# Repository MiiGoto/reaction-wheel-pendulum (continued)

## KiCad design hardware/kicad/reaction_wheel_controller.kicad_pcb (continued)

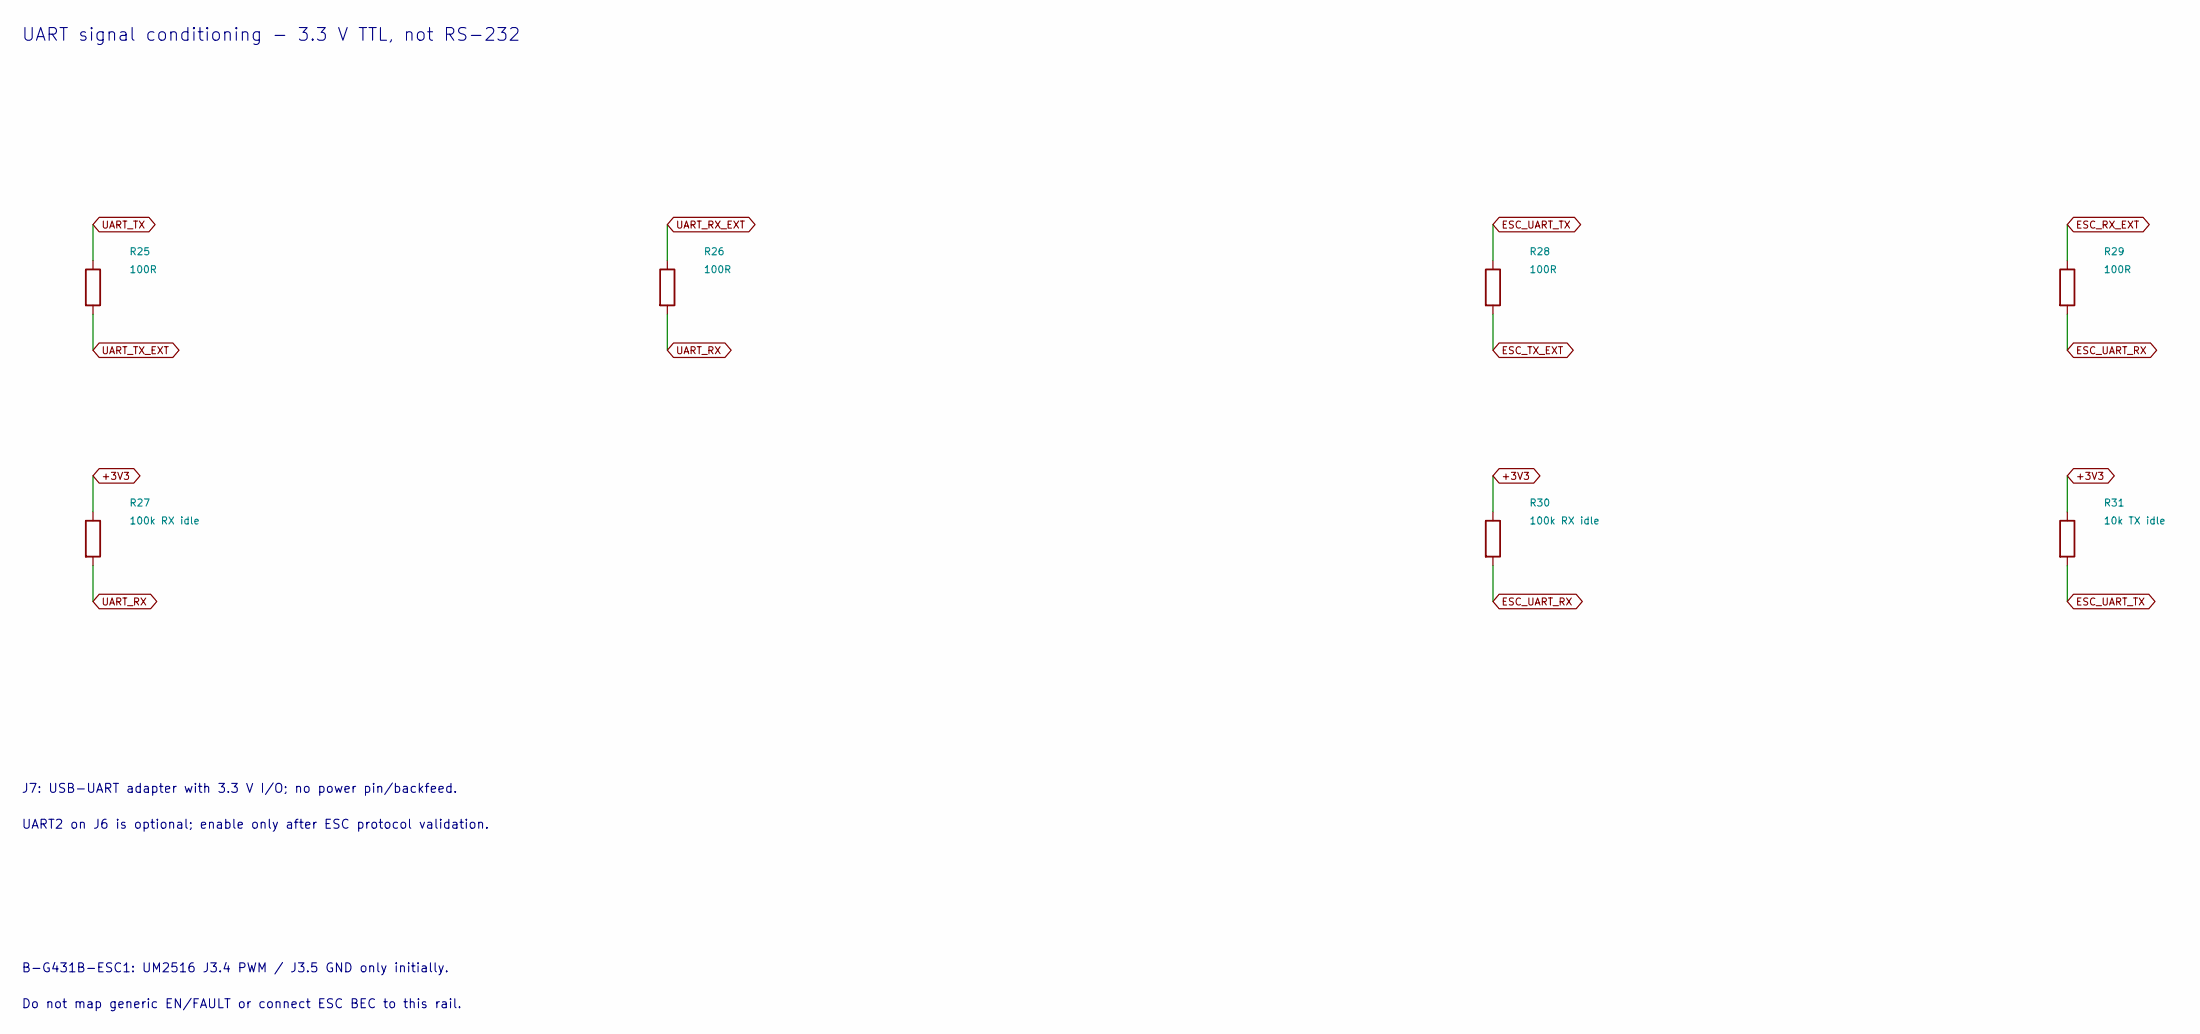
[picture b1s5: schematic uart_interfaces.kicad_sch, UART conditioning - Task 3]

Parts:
R25, R26, R28, R29: 100R; R_0805_2012Metric
R27, R30: 100k RX idle; R_0805_2012Metric
R31: 10k TX idle; R_0805_2012Metric

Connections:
+3V3: R27.1, R30.1, R31.1; also elsewhere on the board
ESC_RX_EXT: R29.1; also elsewhere on the board
ESC_TX_EXT: R28.2; also elsewhere on the board
ESC_UART_RX: R29.2, R30.2; also elsewhere on the board
ESC_UART_TX: R28.1, R31.2; also elsewhere on the board
UART_RX: R26.2, R27.2; also elsewhere on the board
UART_RX_EXT: R26.1; also elsewhere on the board
UART_TX: R25.1; also elsewhere on the board
UART_TX_EXT: R25.2; also elsewhere on the board

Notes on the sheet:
UART signal conditioning - 3.3 V TTL, not RS-232
J7: USB-UART adapter with 3.3 V I/O; no power pin/backfeed.
UART2 on J6 is optional; enable only after ESC protocol validation.
B-G431B-ESC1: UM2516 J3.4 PWM / J3.5 GND only initially.
Do not map generic EN/FAULT or connect ESC BEC to this rail.

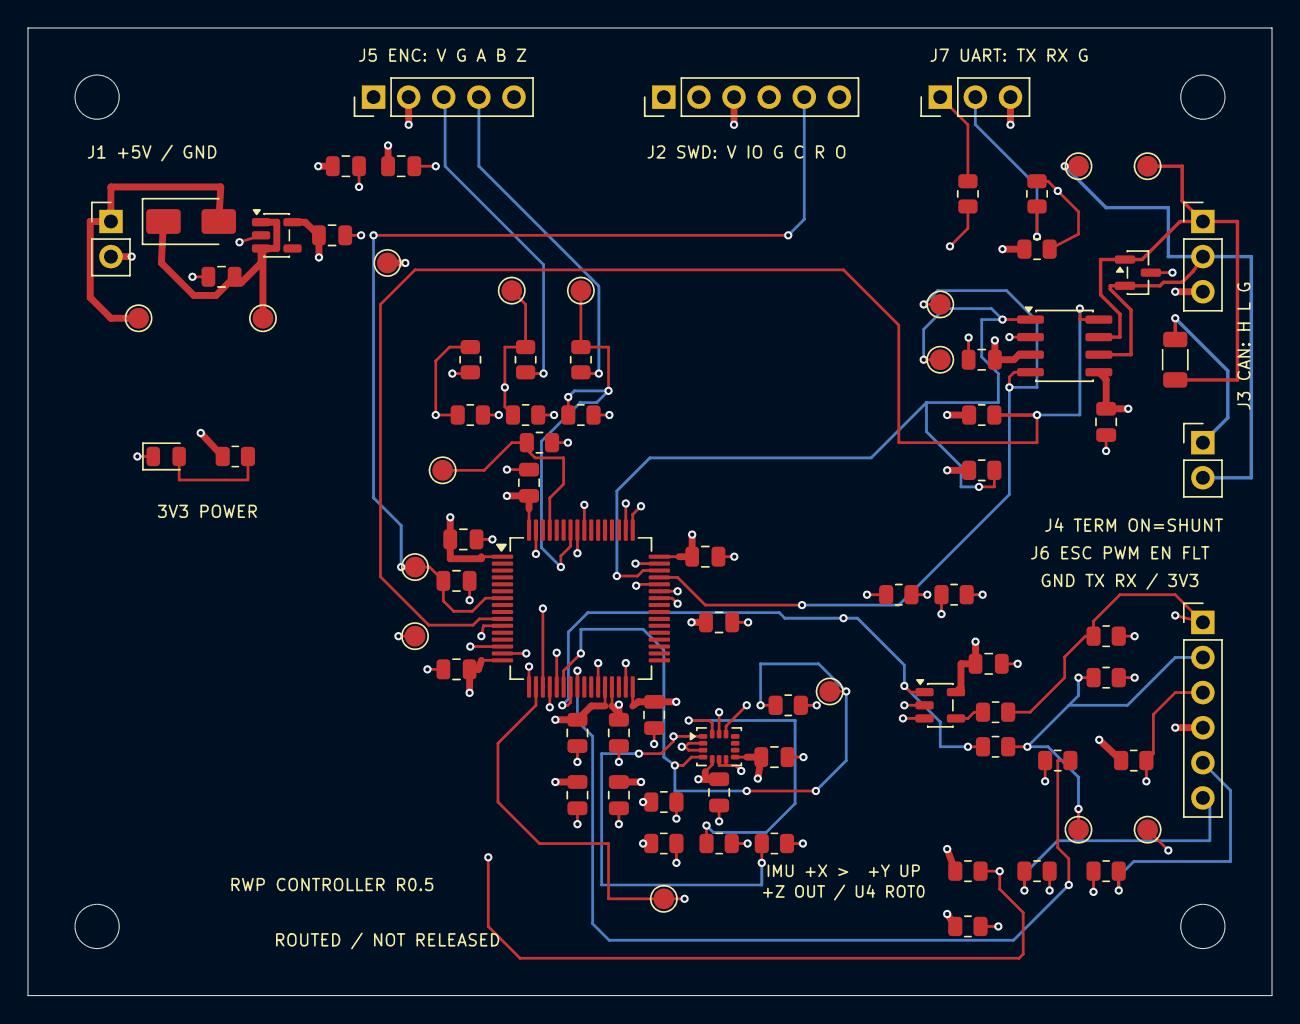
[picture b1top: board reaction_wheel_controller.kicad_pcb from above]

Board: 4 copper layers, 90.0 x 70.0 mm, 86 parts (0 on the bottom side), 42 nets.
